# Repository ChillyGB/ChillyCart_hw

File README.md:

# ChillyCart (hardware)

A simple rp2350 based gameboy(color) cartdrige complete with:
- SPI SD card
- RTC 
- Accelerometer
- 8 MB of PSRAM

## ⚠️ Warning: untested design, DO NOT USE

| Parameter       | Value                 |
|-----------------|-----------------------|
| PCB Layers      | 2                     |
| Surface Finish  | ENIG(w/ gold fingers) |
| Board Thickness | 1.0mm                 |
| Meow            | prrrr                 |

## TODO: 
- *Test if the design actually works and doesn't blow up*
- Route power and PSRAM/flash data lines in a cleaner way
- Provide BOM ( and cost optimize some components )

## Soures of inspiration 
- [kicad-gamepaks](https://github.com/djedditt/kicad-gamepaks) - cartrdge connector and edge cuts
- [Croco Cartridge](https://github.com/shilga/rp2040-gameboy-cartridge) - voltage translator
- [SummerCart](https://github.com/Polprzewodnikowy/SummerCart64) - RTC and power mux

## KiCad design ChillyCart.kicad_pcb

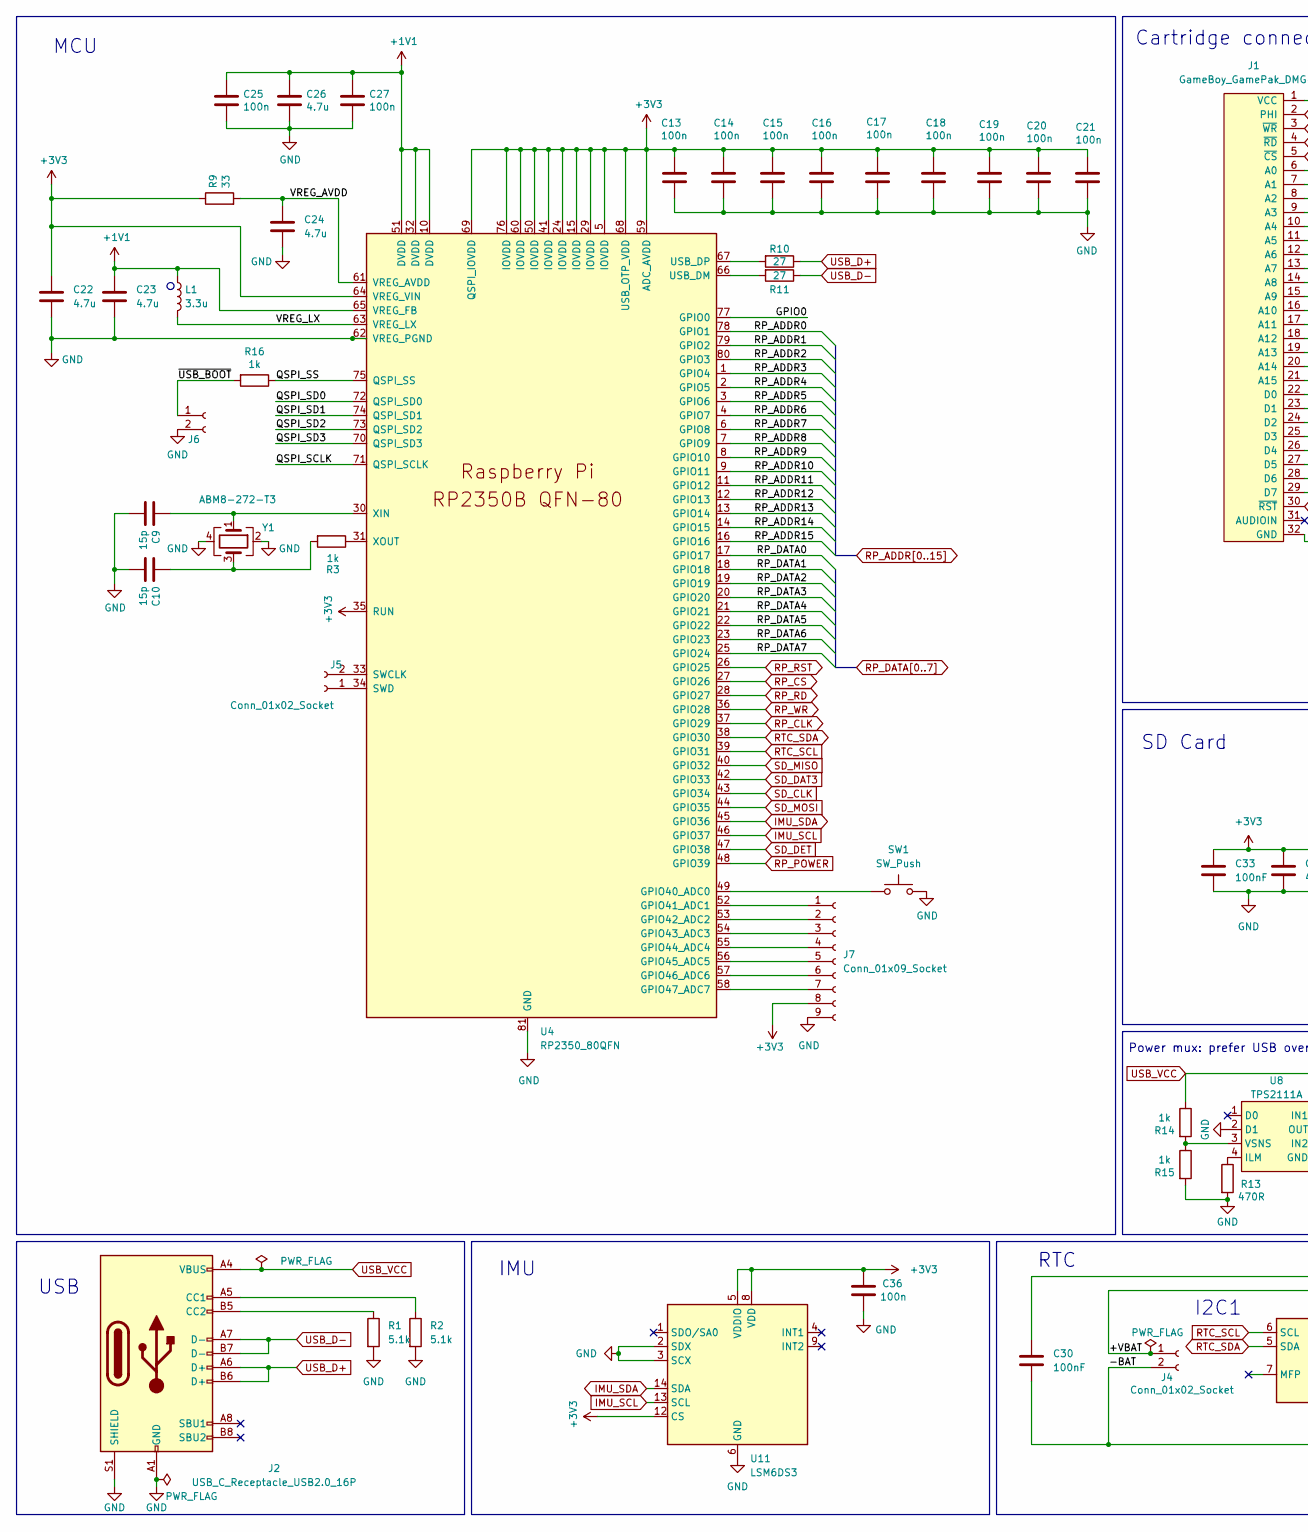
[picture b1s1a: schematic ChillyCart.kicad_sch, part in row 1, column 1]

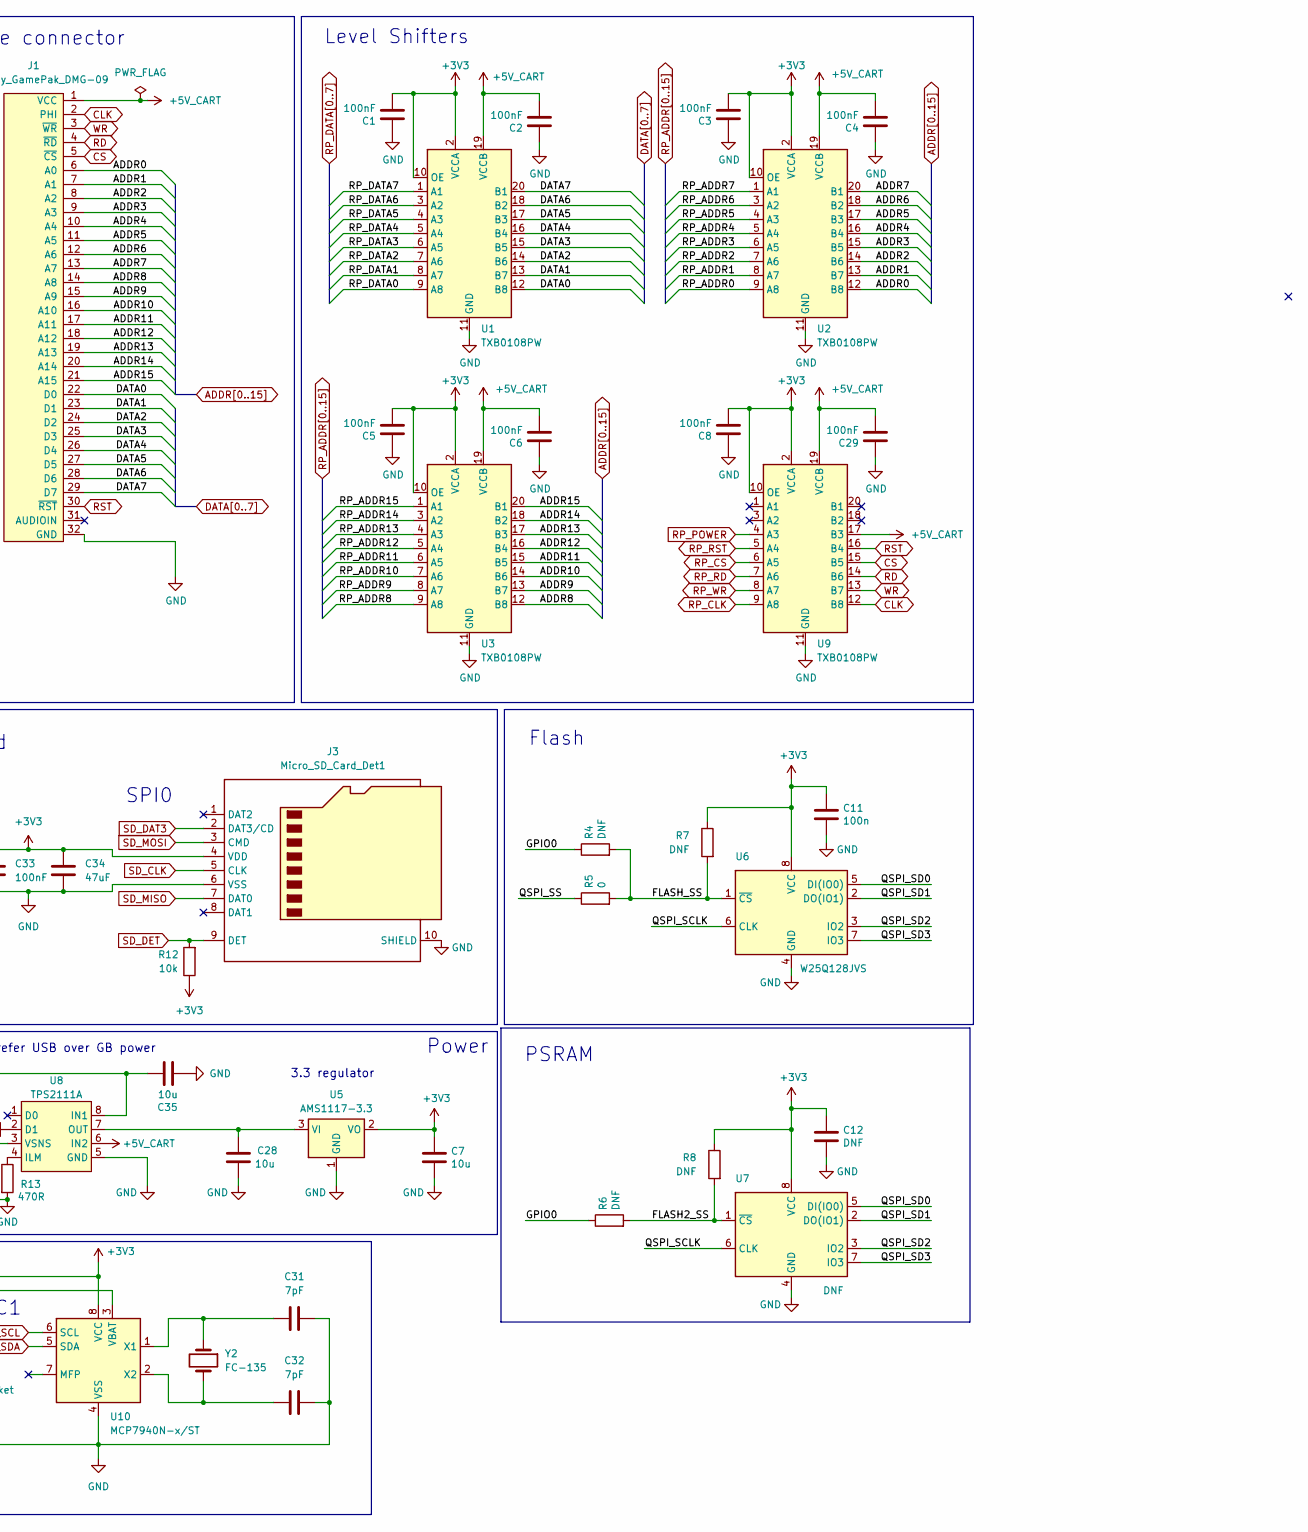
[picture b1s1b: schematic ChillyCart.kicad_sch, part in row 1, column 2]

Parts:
C1, C2, C3, C4, C5, C6, C8, C29, C30, C33: 100nF; C_0402_1005Metric_Pad0.74x0.62mm_HandSolder
C7, C28, C35: 10u; C_0402_1005Metric_Pad0.74x0.62mm_HandSolder
C9, C10: 15p; C_0402_1005Metric_Pad0.74x0.62mm_HandSolder
C11, C13, C14, C15, C16, C17, C18, C19, C20, C21, C25, C27, C36: 100n; C_0402_1005Metric_Pad0.74x0.62mm_HandSolder
C12: DNF; C_0402_1005Metric_Pad0.74x0.62mm_HandSolder
C22, C23, C24, C26: 4.7u; C_0402_1005Metric_Pad0.74x0.62mm_HandSolder
C31, C32: 7pF; C_0402_1005Metric_Pad0.74x0.62mm_HandSolder
C34: 47uF; C_0402_1005Metric_Pad0.74x0.62mm_HandSolder
J1: GameBoy_GamePak_DMG-09; GameBoy_GamePak_DMG-09_P1.50mm_Edge
J2: USB_C_Receptacle_USB2.0_16P; USB_C_Receptacle_G-Switch_GT-USB-7010ASV
J3: Micro_SD_Card_Det1; TF-015
J4, J5, J6: Conn_01x02_Socket; TestPoint_2Pads_Pitch2.54mm_Drill0.8mm
J7: Conn_01x09_Socket; PinHeader_1x09_P1.00mm_Vertical
L1: 3.3u; L_pol_2016
R1, R2: 5.1k; R_0402_1005Metric_Pad0.72x0.64mm_HandSolder
R3, R14, R15, R16: 1k; R_0402_1005Metric_Pad0.72x0.64mm_HandSolder
R4, R6, R7, R8: DNF; R_0402_1005Metric_Pad0.72x0.64mm_HandSolder
R5: 0; R_0402_1005Metric_Pad0.72x0.64mm_HandSolder
R9: 33; R_0402_1005Metric_Pad0.72x0.64mm_HandSolder
R10, R11: 27; R_0402_1005Metric_Pad0.72x0.64mm_HandSolder
R12: 10k; R_0402_1005Metric_Pad0.72x0.64mm_HandSolder
R13: 470R; R_0402_1005Metric_Pad0.72x0.64mm_HandSolder
SW1: SW_Push; SW_Push_1P1T_XKB_TS-1187A
U1, U2, U3, U9: TXB0108PW; TSSOP-20_4.4x6.5mm_P0.65mm; LCSC C53406
U4: RP2350_80QFN; RP2350-QFN-80-1EP_10x10_P0.4mm_EP3.4x3.4mm_ThermalVias
U5: AMS1117-3.3; SOT-223-3_TabPin2
U6: W25Q128JVS; SOIC-8_5.23x5.23mm_P1.27mm
U7: DNF; SOIC-8_5.23x5.23mm_P1.27mm
U8: TPS2111A; TSSOP-8_4.4x3mm_P0.65mm
U10: MCP7940N-x/ST; TSSOP-8_4.4x3mm_P0.65mm
U11: LSM6DS3; LGA-14_3x2.5mm_P0.5mm_LayoutBorder3x4y
Y1: ABM8-272-T3; Crystal_SMD_3225-4Pin_3.2x2.5mm
Y2: FC-135; Crystal_SMD_3215-2Pin_3.2x1.5mm

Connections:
+1V1: C23.1, C25.1, C26.1, C27.1, L1.1, U4.10 (DVDD), U4.32 (DVDD), U4.51 (DVDD), U4.65 (VREG_FB)
+3V3: C1.2, C3.2, C5.2, C7.1, C8.2, C11.1, C12.1, C13.1, C14.1, C15.1, C16.1, C17.1, C18.1, C19.1, C20.1, C21.1, C22.1, C30.1, C33.1, C34.1, C36.1, J3.4 (VDD), J7.8, R7.1, R8.1, R9.1, R12.1, U1.2 (VCCA), U1.10 (OE), U2.2 (VCCA), U2.10 (OE), U3.2 (VCCA), U3.10 (OE), U4.5 (IOVDD), U4.15 (IOVDD), U4.24 (IOVDD), U4.29 (IOVDD), U4.35 (RUN), U4.41 (IOVDD), U4.50 (IOVDD), U4.59 (ADC_AVDD), U4.60 (IOVDD), U4.64 (VREG_VIN), U4.68 (USB_OTP_VDD), U4.69 (QSPI_IOVDD), U4.76 (IOVDD), U5.2 (VO), U6.8 (VCC), U7.8 (VCC), U9.2 (VCCA), U9.10 (OE), U10.8 (VCC), U11.5 (VDDIO), U11.8 (VDD), U11.12 (CS)
+5V_CART: C2.2, C4.2, C6.2, C29.2, J1.1 (VCC), U1.19 (VCCB), U2.19 (VCCB), U3.19 (VCCB), U8.6 (IN2), U9.17 (B3), U9.19 (VCCB)
/+VBAT: J4.1, U10.3 (VBAT)
/FLASH2_SS: R6.2, R8.2, U7.1 (~CS)
/FLASH_SS: R4.2, R5.2, R7.2, U6.1 (~CS)
/GPIO0: R4.1, R6.1, U4.77 (GPIO0)
/QSPI_SCLK: U4.71 (QSPI_SCLK), U6.6 (CLK), U7.6 (CLK)
/QSPI_SD0: U4.72 (QSPI_SD0), U6.5 (DI(IO0)), U7.5 (DI(IO0))
/QSPI_SD1: U4.74 (QSPI_SD1), U6.2 (DO(IO1)), U7.2 (DO(IO1))
/QSPI_SD2: U4.73 (QSPI_SD2), U6.3 (IO2), U7.3 (IO2)
/QSPI_SD3: U4.70 (QSPI_SD3), U6.7 (IO3), U7.7 (IO3)
/QSPI_SS: R5.1, R16.1, U4.75 (QSPI_SS)
/VREG_AVDD: C24.1, R9.2, U4.61 (VREG_AVDD)
/VREG_LX: L1.2, U4.63 (VREG_LX)
/~USB_BOOT: J6.1, R16.2
ADDR0: J1.6 (A0), U2.12 (B8)
ADDR1: J1.7 (A1), U2.13 (B7)
ADDR2: J1.8 (A2), U2.14 (B6)
ADDR3: J1.9 (A3), U2.15 (B5)
ADDR4: J1.10 (A4), U2.16 (B4)
ADDR5: J1.11 (A5), U2.17 (B3)
ADDR6: J1.12 (A6), U2.18 (B2)
ADDR7: J1.13 (A7), U2.20 (B1)
ADDR8: J1.14 (A8), U3.12 (B8)
ADDR9: J1.15 (A9), U3.13 (B7)
ADDR10: J1.16 (A10), U3.14 (B6)
ADDR11: J1.17 (A11), U3.15 (B5)
ADDR12: J1.18 (A12), U3.16 (B4)
ADDR13: J1.19 (A13), U3.17 (B3)
ADDR14: J1.20 (A14), U3.18 (B2)
ADDR15: J1.21 (A15), U3.20 (B1)
CLK: J1.2 (PHI), U9.12 (B8)
CS: J1.5 (~CS), U9.15 (B5)
DATA0: J1.22 (D0), U1.12 (B8)
DATA1: J1.23 (D1), U1.13 (B7)
DATA2: J1.24 (D2), U1.14 (B6)
DATA3: J1.25 (D3), U1.15 (B5)
DATA4: J1.26 (D4), U1.16 (B4)
DATA5: J1.27 (D5), U1.17 (B3)
DATA6: J1.28 (D6), U1.18 (B2)
DATA7: J1.29 (D7), U1.20 (B1)
GND: C1.1, C2.1, C3.1, C4.1, C5.1, C6.1, C7.2, C8.1, C9.2, C10.2, C11.2, C12.2, C13.2, C14.2, C15.2, C16.2, C17.2, C18.2, C19.2, C20.2, C21.2, C22.2, C23.2, C24.2, C25.2, C26.2, C27.2, C28.2, C29.1, C30.2, C31.2, C32.1, C33.2, C34.2, C35.2, C36.2, J1.32 (GND), J2.A1 (GND), J2.A12 (GND), J2.B1 (GND), J2.B12 (GND), J2.S1 (SHIELD), J3.6 (VSS), J3.10 (SHIELD), J4.2, J6.2, J7.9, R1.2, R2.2, R13.2, R15.2, SW1.2, U1.11 (GND), U2.11 (GND), U3.11 (GND), U4.62 (VREG_PGND), U4.81 (GND), U5.1 (GND), U6.4 (GND), U7.4 (GND), U8.2 (D1), U8.5 (GND), U9.11 (GND), U10.4 (VSS), U11.2 (SDX), U11.3 (SCX), U11.6 (GND), U11.7 (GND), Y1.2, Y1.4
IMU_SCL: U4.46 (GPIO37), U11.13 (SCL)
IMU_SDA: U4.45 (GPIO36), U11.14 (SDA)
unnamed: C10.1, R3.2, Y1.3
unnamed: J2.A5 (CC1), R2.1
unnamed: J2.B5 (CC2), R1.1
unnamed: J5.1, U4.34 (SWD)
unnamed: J5.2, U4.33 (SWCLK)
unnamed: J7.1, U4.52 (GPIO41_ADC1)
unnamed: J7.2, U4.53 (GPIO42_ADC2)
unnamed: J7.3, U4.54 (GPIO43_ADC3)
unnamed: J7.4, U4.55 (GPIO44_ADC4)
unnamed: J7.5, U4.56 (GPIO45_ADC5)
unnamed: J7.6, U4.57 (GPIO46_ADC6)
unnamed: J7.7, U4.58 (GPIO47_ADC7)
unnamed: SW1.1, U4.49 (GPIO40_ADC0)
unnamed: R11.2, U4.66 (USB_DM)
unnamed: R10.2, U4.67 (USB_DP)
unnamed: C9.1, U4.30 (XIN), Y1.1
unnamed: R3.1, U4.31 (XOUT)
unnamed: C28.1, U5.3 (VI), U8.7 (OUT)
unnamed: R13.1, U8.4 (ILM)
unnamed: R14.2, R15.1, U8.3 (VSNS)
unnamed: C31.1, U10.1 (X1), Y2.1
unnamed: C32.2, U10.2 (X2), Y2.2
RD: J1.4 (~RD), U9.14 (B6)
RP_ADDR0: U2.9 (A8), U4.78 (GPIO1)
RP_ADDR1: U2.8 (A7), U4.79 (GPIO2)
RP_ADDR2: U2.7 (A6), U4.80 (GPIO3)
RP_ADDR3: U2.6 (A5), U4.1 (GPIO4)
RP_ADDR4: U2.5 (A4), U4.2 (GPIO5)
RP_ADDR5: U2.4 (A3), U4.3 (GPIO6)
RP_ADDR6: U2.3 (A2), U4.4 (GPIO7)
RP_ADDR7: U2.1 (A1), U4.6 (GPIO8)
RP_ADDR8: U3.9 (A8), U4.7 (GPIO9)
RP_ADDR9: U3.8 (A7), U4.8 (GPIO10)
RP_ADDR10: U3.7 (A6), U4.9 (GPIO11)
RP_ADDR11: U3.6 (A5), U4.11 (GPIO12)
RP_ADDR12: U3.5 (A4), U4.12 (GPIO13)
RP_ADDR13: U3.4 (A3), U4.13 (GPIO14)
RP_ADDR14: U3.3 (A2), U4.14 (GPIO15)
RP_ADDR15: U3.1 (A1), U4.16 (GPIO16)
RP_CLK: U4.37 (GPIO29), U9.9 (A8)
RP_CS: U4.27 (GPIO26), U9.6 (A5)
RP_DATA0: U1.9 (A8), U4.17 (GPIO17)
RP_DATA1: U1.8 (A7), U4.18 (GPIO18)
RP_DATA2: U1.7 (A6), U4.19 (GPIO19)
RP_DATA3: U1.6 (A5), U4.20 (GPIO20)
RP_DATA4: U1.5 (A4), U4.21 (GPIO21)
RP_DATA5: U1.4 (A3), U4.22 (GPIO22)
RP_DATA6: U1.3 (A2), U4.23 (GPIO23)
RP_DATA7: U1.1 (A1), U4.25 (GPIO24)
RP_POWER: U4.48 (GPIO39), U9.4 (A3)
RP_RD: U4.28 (GPIO27), U9.7 (A6)
RP_RST: U4.26 (GPIO25), U9.5 (A4)
RP_WR: U4.36 (GPIO28), U9.8 (A7)
RST: J1.30 (~RST), U9.16 (B4)
RTC_SCL: U4.39 (GPIO31), U10.6 (SCL)
RTC_SDA: U4.38 (GPIO30), U10.5 (SDA)
SD_CLK: J3.5 (CLK), U4.43 (GPIO34)
SD_DAT3: J3.2 (DAT3/CD), U4.42 (GPIO33)
SD_DET: J3.9 (DET), R12.2, U4.47 (GPIO38)
SD_MISO: J3.7 (DAT0), U4.40 (GPIO32)
SD_MOSI: J3.3 (CMD), U4.44 (GPIO35)
USB_D+: J2.A6 (D+), J2.B6 (D+), R10.1
USB_D-: J2.A7 (D-), J2.B7 (D-), R11.1
USB_VCC: C35.1, J2.A4 (VBUS), J2.A9 (VBUS), J2.B4 (VBUS), J2.B9 (VBUS), R14.1, U8.8 (IN1)
WR: J1.3 (~WR), U9.13 (B7)

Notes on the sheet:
Level Shifters
I2C1
3.3 regulator
Power mux: prefer USB over GB power
Power
SPI0
SD Card
Cartridge connector
RTC
USB
IMU
Flash
MCU
PSRAM

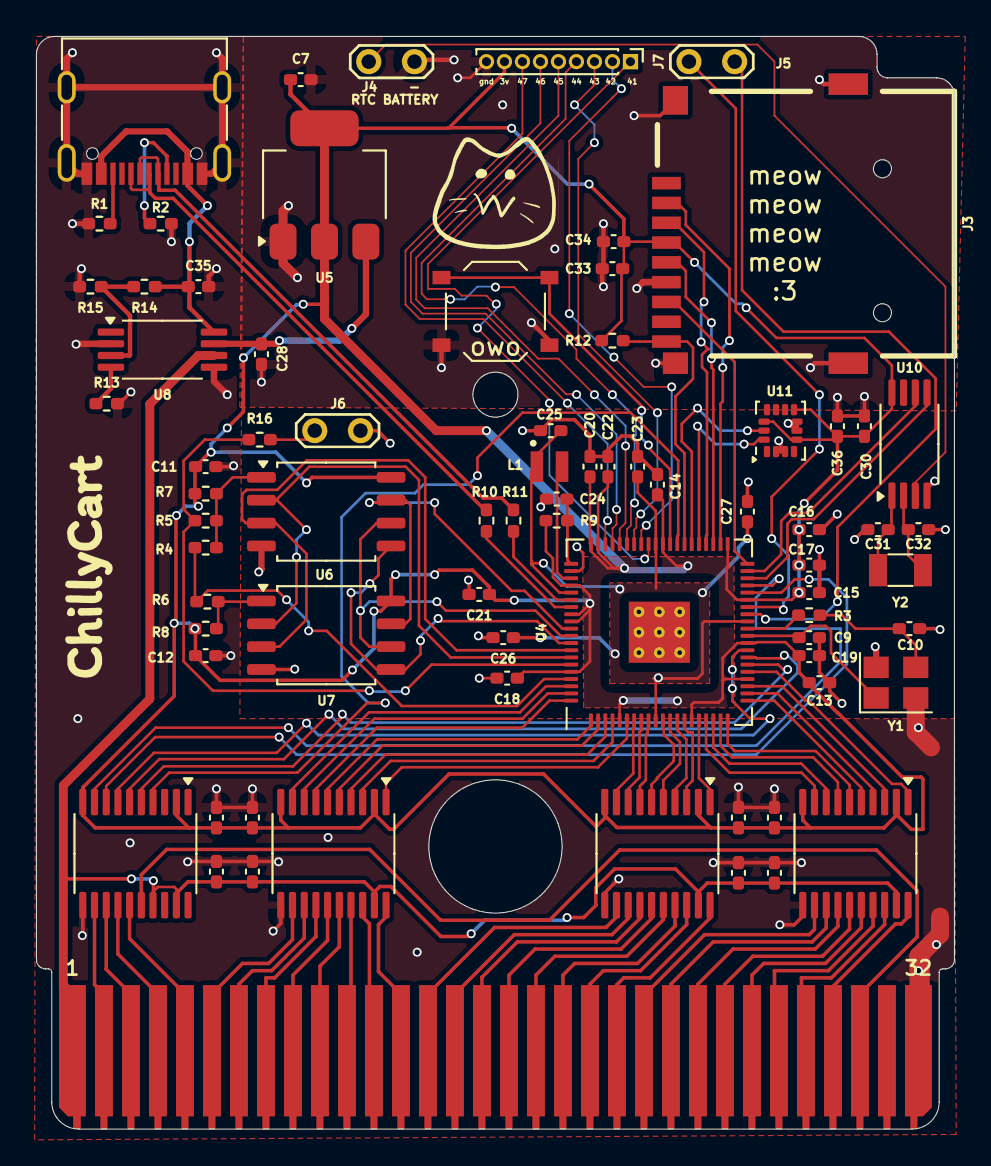
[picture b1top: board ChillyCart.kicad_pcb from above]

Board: 2 copper layers, 51.0 x 60.7 mm, 74 parts (0 on the bottom side), 110 nets.

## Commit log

2025-01-22 Inital commit
2025-01-22 Added psram,flash,rtc,sd
2025-01-23 Add IMU, power mux and cleanup schematic
2025-01-24 Add debug connectors and push button, fix ERC errors
2025-01-24 Initial routing
2025-01-25 Finish routingn
2025-01-26 Tidy up silkscreen
2025-02-02 jlc gerber export settings
2025-02-02 Added README
2025-02-02 Create LICENSE
2025-02-02 Add image to README
